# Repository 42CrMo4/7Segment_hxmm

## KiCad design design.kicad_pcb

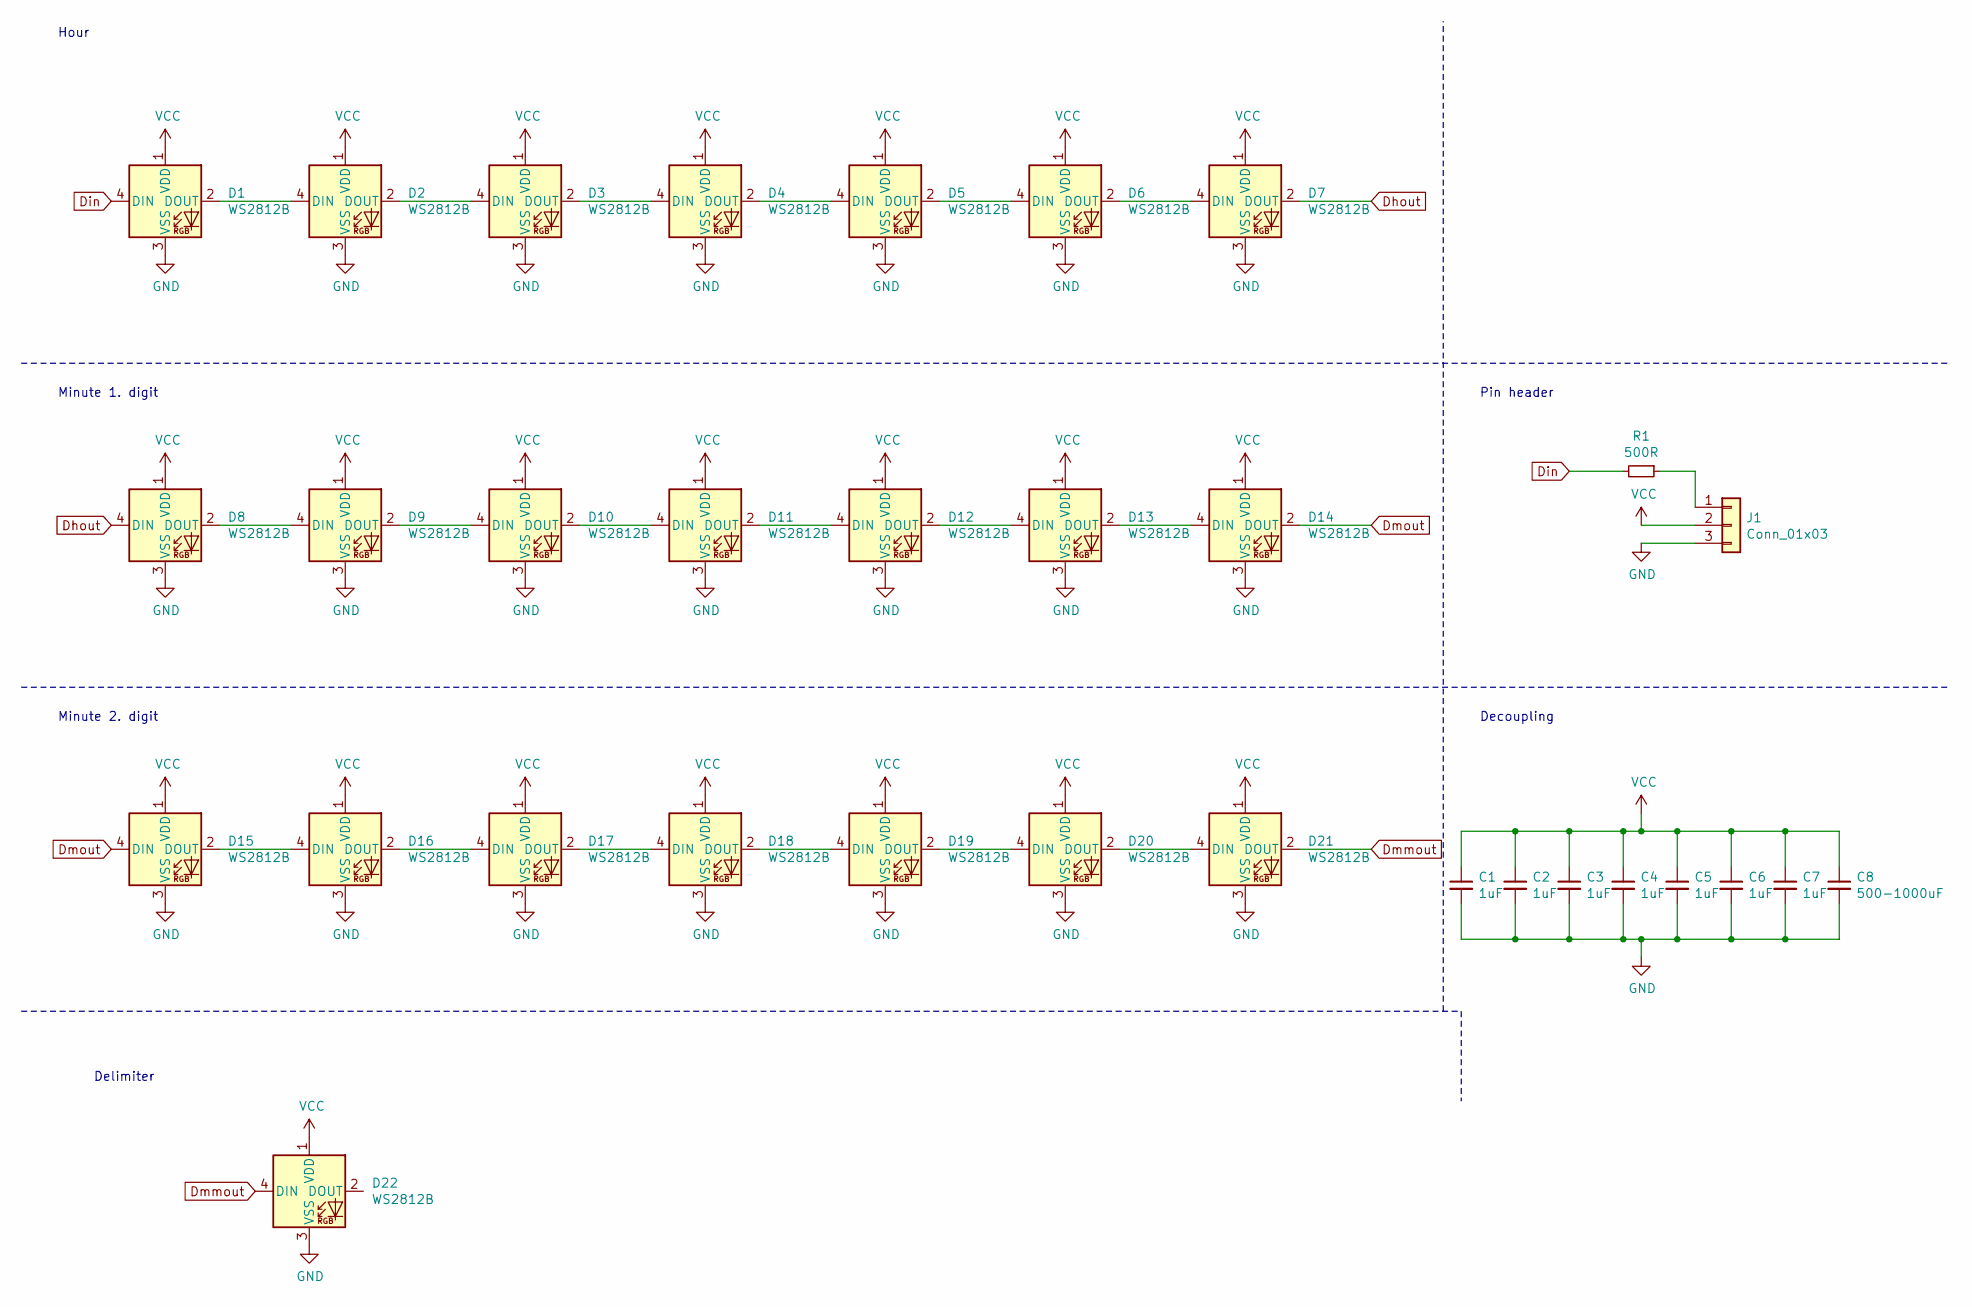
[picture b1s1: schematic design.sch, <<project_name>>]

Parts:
C1, C2, C3, C4, C5, C6, C7: 1uF; C_0805_2012Metric
C8: 500-1000uF; C_2225_5664Metric
D1, D2, D3, D4, D5, D6, D7, D8, D9, D10, D11, D12, D13, D14, D15, D16, D17, D18, D19, D20, D21, D22: WS2812B; LED_WS2812B_PLCC4_5.0x5.0mm_P3.2mm
J1: Conn_01x03; PinHeader_1x03_P2.54mm_Vertical_SMD_Pin1Left
R1: 500R; R_0805_2012Metric

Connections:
Dhout: D7.2 (DOUT), D8.4 (DIN)
Din: D1.4 (DIN), R1.2
Dmmout: D21.2 (DOUT), D22.4 (DIN)
Dmout: D14.2 (DOUT), D15.4 (DIN)
GND: C1.2, C2.2, C3.2, C4.2, C5.2, C6.2, C7.2, C8.2, D1.3 (VSS), D2.3 (VSS), D3.3 (VSS), D4.3 (VSS), D5.3 (VSS), D6.3 (VSS), D7.3 (VSS), D8.3 (VSS), D9.3 (VSS), D10.3 (VSS), D11.3 (VSS), D12.3 (VSS), D13.3 (VSS), D14.3 (VSS), D15.3 (VSS), D16.3 (VSS), D17.3 (VSS), D18.3 (VSS), D19.3 (VSS), D20.3 (VSS), D21.3 (VSS), D22.3 (VSS), J1.3
unnamed: D1.2 (DOUT), D2.4 (DIN)
unnamed: D2.2 (DOUT), D3.4 (DIN)
unnamed: D3.2 (DOUT), D4.4 (DIN)
unnamed: D4.2 (DOUT), D5.4 (DIN)
unnamed: D5.2 (DOUT), D6.4 (DIN)
unnamed: D6.2 (DOUT), D7.4 (DIN)
unnamed: D8.2 (DOUT), D9.4 (DIN)
unnamed: D10.2 (DOUT), D11.4 (DIN)
unnamed: D9.2 (DOUT), D10.4 (DIN)
unnamed: D11.2 (DOUT), D12.4 (DIN)
unnamed: D12.2 (DOUT), D13.4 (DIN)
unnamed: D13.2 (DOUT), D14.4 (DIN)
unnamed: D15.2 (DOUT), D16.4 (DIN)
unnamed: D16.2 (DOUT), D17.4 (DIN)
unnamed: D17.2 (DOUT), D18.4 (DIN)
unnamed: D18.2 (DOUT), D19.4 (DIN)
unnamed: D19.2 (DOUT), D20.4 (DIN)
unnamed: D20.2 (DOUT), D21.4 (DIN)
unnamed: J1.1, R1.1
VCC: C1.1, C2.1, C3.1, C4.1, C5.1, C6.1, C7.1, C8.1, D1.1 (VDD), D2.1 (VDD), D3.1 (VDD), D4.1 (VDD), D5.1 (VDD), D6.1 (VDD), D7.1 (VDD), D8.1 (VDD), D9.1 (VDD), D10.1 (VDD), D11.1 (VDD), D12.1 (VDD), D13.1 (VDD), D14.1 (VDD), D15.1 (VDD), D16.1 (VDD), D17.1 (VDD), D18.1 (VDD), D19.1 (VDD), D20.1 (VDD), D21.1 (VDD), D22.1 (VDD), J1.2

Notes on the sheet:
Hour
Minute 1. digit
Minute 2. digit
Decoupling
Pin header
Delimiter

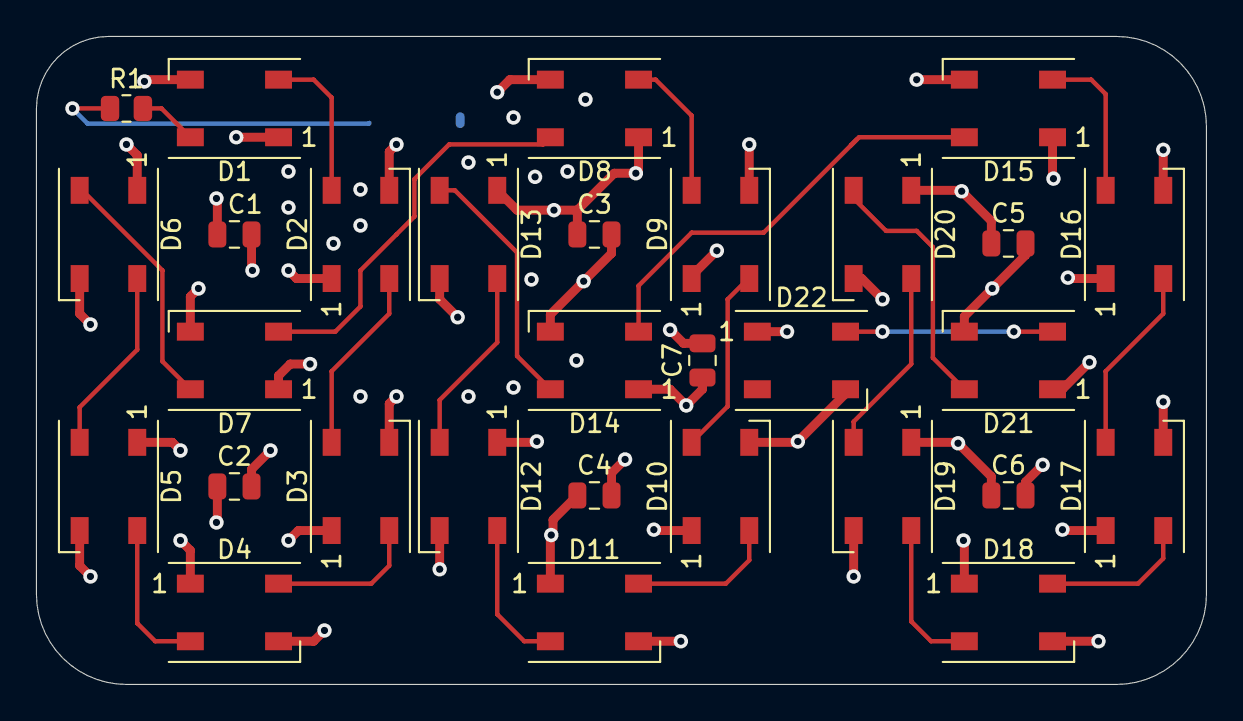
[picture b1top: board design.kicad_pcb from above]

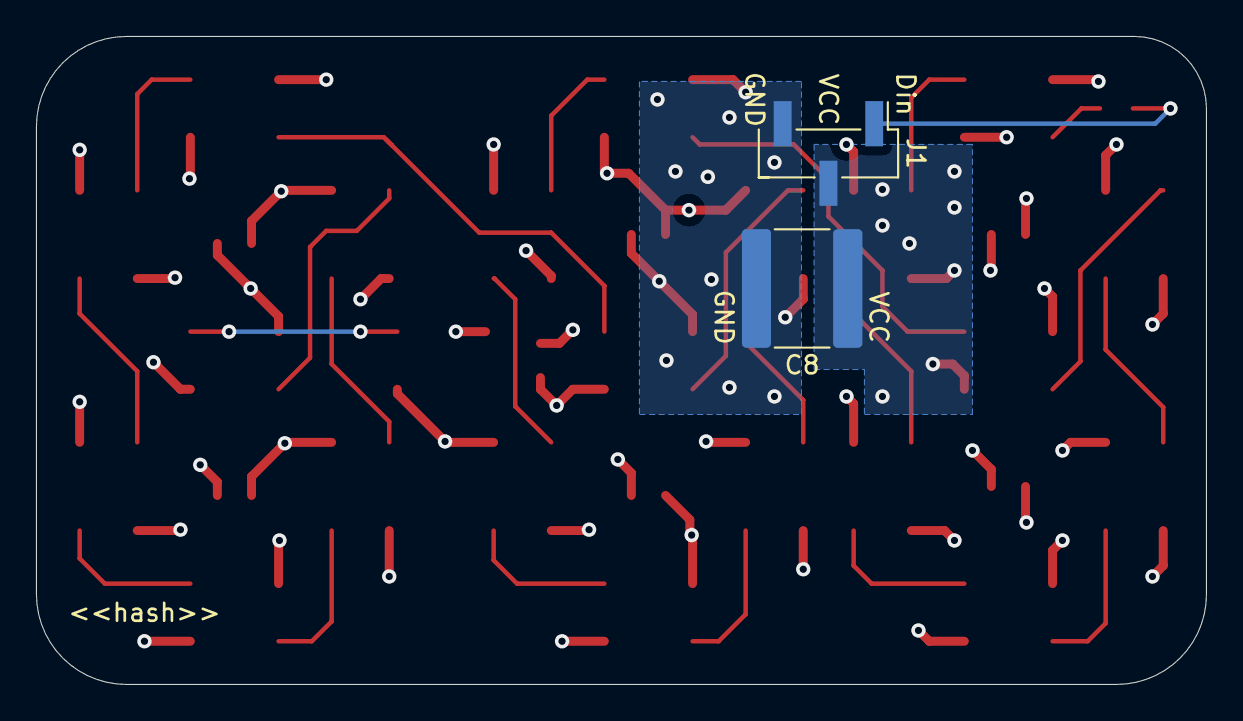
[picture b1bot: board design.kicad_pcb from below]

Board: 4 copper layers, 65.0 x 36.0 mm, 32 parts (2 on the bottom side), 25 nets.

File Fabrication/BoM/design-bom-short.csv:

Row,Description,Part,References,Value,Footprint,Quantity Per PCB,Status,Datasheet
1,"Unpolarized capacitor, small symbol",C_Small,C1 C2 C3 C4 C5 C6 C7,1uF,C_0805_2012Metric,7, ,~
2,"Unpolarized capacitor, small symbol",C_Small,C8,500-1000uF,C_2225_5664Metric,1, ,~
3,RGB LED with integrated controller,WS2812B,D1 D2 D3 D4 D5 D6 D7 D8 D9 D10 D11 D12 D13 D14 D15 D16 D17 D18 D19 D20 D21 D22,WS2812B,LED_WS2812B_PLCC4_5.0x5.0mm_P3.2mm,22, ,https://cdn-shop.adafruit.com/datasheets/WS2812B.pdf
4,"Generic connector, single row, 01x03, script generated (kicad-library-utils/schlib/autogen/connector/)",Conn_01x03,J1,Conn_01x03,PinHeader_1x03_P2.54mm_Vertical_SMD_Pin1Left,1, ,~
5,"Resistor, small symbol",R_Small,R1,500R,R_0805_2012Metric,1, ,~

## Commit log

2022-01-08 init
2022-01-08 SCH: add power pins to delimiter
2022-01-08 Update Bom
2022-01-08 PCB: placed components
    and some cosmetic SCH stuff
2022-01-08 SCH: annotation in the segment order
2022-01-08 add pinheader footprint
2022-01-08 PCB: change to 4 layer
2022-01-08 PCB: Layout Hour
2022-01-08 PCB: mm layout
2022-01-08 PCB: Silkscreen
2022-01-08 Kibot: show components on png front
2022-01-08 Kibot: add render from 3D view
2022-01-08 WF: add 3dview output
2022-01-08 use kicad_auto dev
2022-01-08 add zoon and orthographic to 3drender
2022-01-08 PCB: make edgecut bigger
2022-01-08 WF: add 3dview to auto commit
2022-01-08 Kibot: revert PCBdraw output to show components
2022-01-08 PCB: add rounded corners
2022-01-08 PCB: Dimension on DWG layer
2022-01-08 PCB: center pcb for rendering
2022-01-09 added big capacitor and resistor @input
2022-01-09 PCB: fix DRC error
2022-01-09 PCB: show DWG layer in editor
    to center the pcb in the 3D viewer correct for the 3Drendering
2022-01-09 PCB: add marking VCC/GND
2022-01-18 PCB: connect D8/3 to GND
    Fix #1
2022-01-18 create Release Note
2022-02-07 init doc
2022-02-07 Deployed 7f0a40e with MkDocs version: 1.2.3
